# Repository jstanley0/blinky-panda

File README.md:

# blinky-panda
an electronic art project, basically

I made this for the design challenge, to learn KiCad better, to test out fabrication of a non-rectangular board, and for soldering practice.

There are 25 LEDs logically arranged in a 5x5 matrix, and a simple timer-driven program that drives them with independent 6-bit software PWM.

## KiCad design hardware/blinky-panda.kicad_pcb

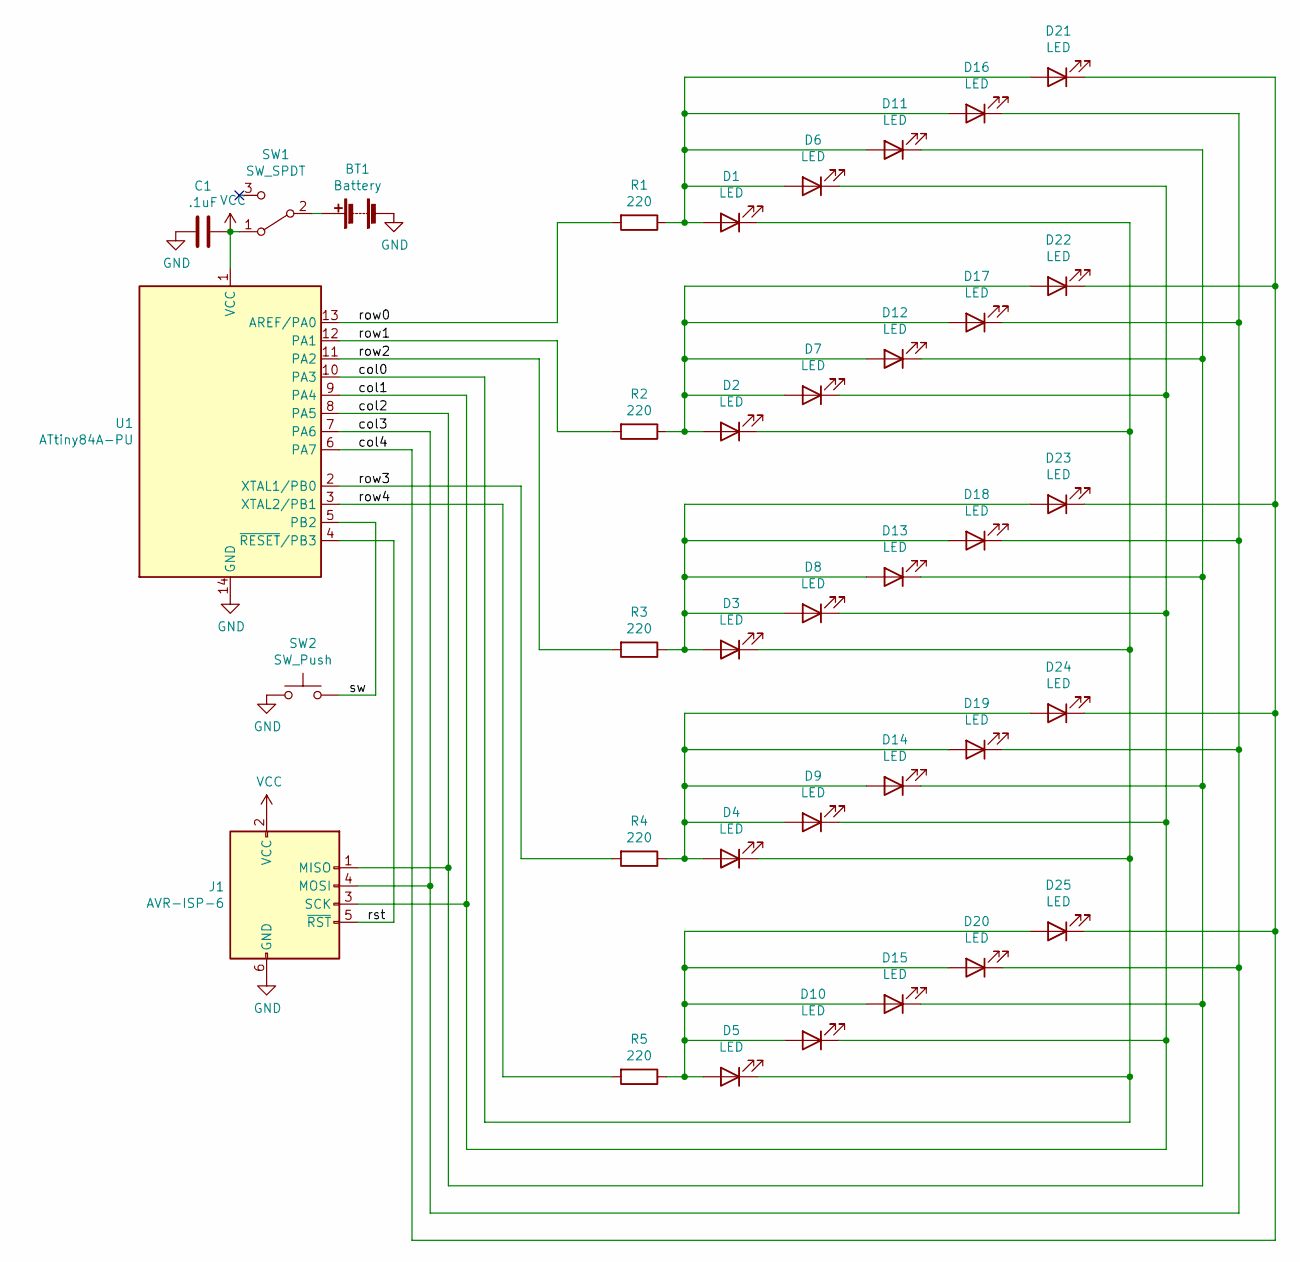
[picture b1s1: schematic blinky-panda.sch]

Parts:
BT1: Battery; PinHeader_1x02_P2.54mm_Vertical
C1: .1uF; C_Disc_D3.0mm_W1.6mm_P2.50mm
D1, D2, D3, D4, D5, D6, D7, D8, D9, D10, D11, D12, D13, D14, D15, D16, D17, D18, D19, D20, D21, D22, D23, D24, D25: LED; LED_D5.0mm_Clear
J1: AVR-ISP-6; PinHeader_2x03_P2.54mm_Vertical
R1, R2, R3, R4, R5: 220; R_Axial_DIN0204_L3.6mm_D1.6mm_P7.62mm_Horizontal
SW1: SW_SPDT; Switch_Slide_11.6x4mm_EG1218
SW2: SW_Push; SW_Tactile_Straight_KSL0Axx1LFTR
U1: ATtiny84A-PU; DIP-14_W7.62mm

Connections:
/col0: D1.1 (K), D2.1 (K), D3.1 (K), D4.1 (K), D5.1 (K), U1.10 (PA3)
/col1: D6.1 (K), D7.1 (K), D8.1 (K), D9.1 (K), D10.1 (K), J1.3 (SCK), U1.9 (PA4)
/col2: D11.1 (K), D12.1 (K), D13.1 (K), D14.1 (K), D15.1 (K), J1.1 (MISO), U1.8 (PA5)
/col3: D16.1 (K), D17.1 (K), D18.1 (K), D19.1 (K), D20.1 (K), J1.4 (MOSI), U1.7 (PA6)
/col4: D21.1 (K), D22.1 (K), D23.1 (K), D24.1 (K), D25.1 (K), U1.6 (PA7)
/row0: R1.2, U1.13 (AREF/PA0)
/row1: R2.2, U1.12 (PA1)
/row2: R3.2, U1.11 (PA2)
/row3: R4.2, U1.2 (XTAL1/PB0)
/row4: R5.2, U1.3 (XTAL2/PB1)
/rst: J1.5 (~RST), U1.4 (~RESET~/PB3)
/sw: SW2.2, U1.5 (PB2)
GND: BT1.2 (-), C1.2, J1.6 (GND), SW2.1, U1.14 (GND)
unnamed: BT1.1 (+), SW1.2 (B)
unnamed: D1.2 (A), D6.2 (A), D11.2 (A), D16.2 (A), D21.2 (A), R1.1
unnamed: D5.2 (A), D10.2 (A), D15.2 (A), D20.2 (A), D25.2 (A), R5.1
unnamed: D2.2 (A), D7.2 (A), D12.2 (A), D17.2 (A), D22.2 (A), R2.1
unnamed: D3.2 (A), D8.2 (A), D13.2 (A), D18.2 (A), D23.2 (A), R3.1
unnamed: D4.2 (A), D9.2 (A), D14.2 (A), D19.2 (A), D24.2 (A), R4.1
VCC: C1.1, J1.2 (VCC), SW1.1 (A), U1.1 (VCC)

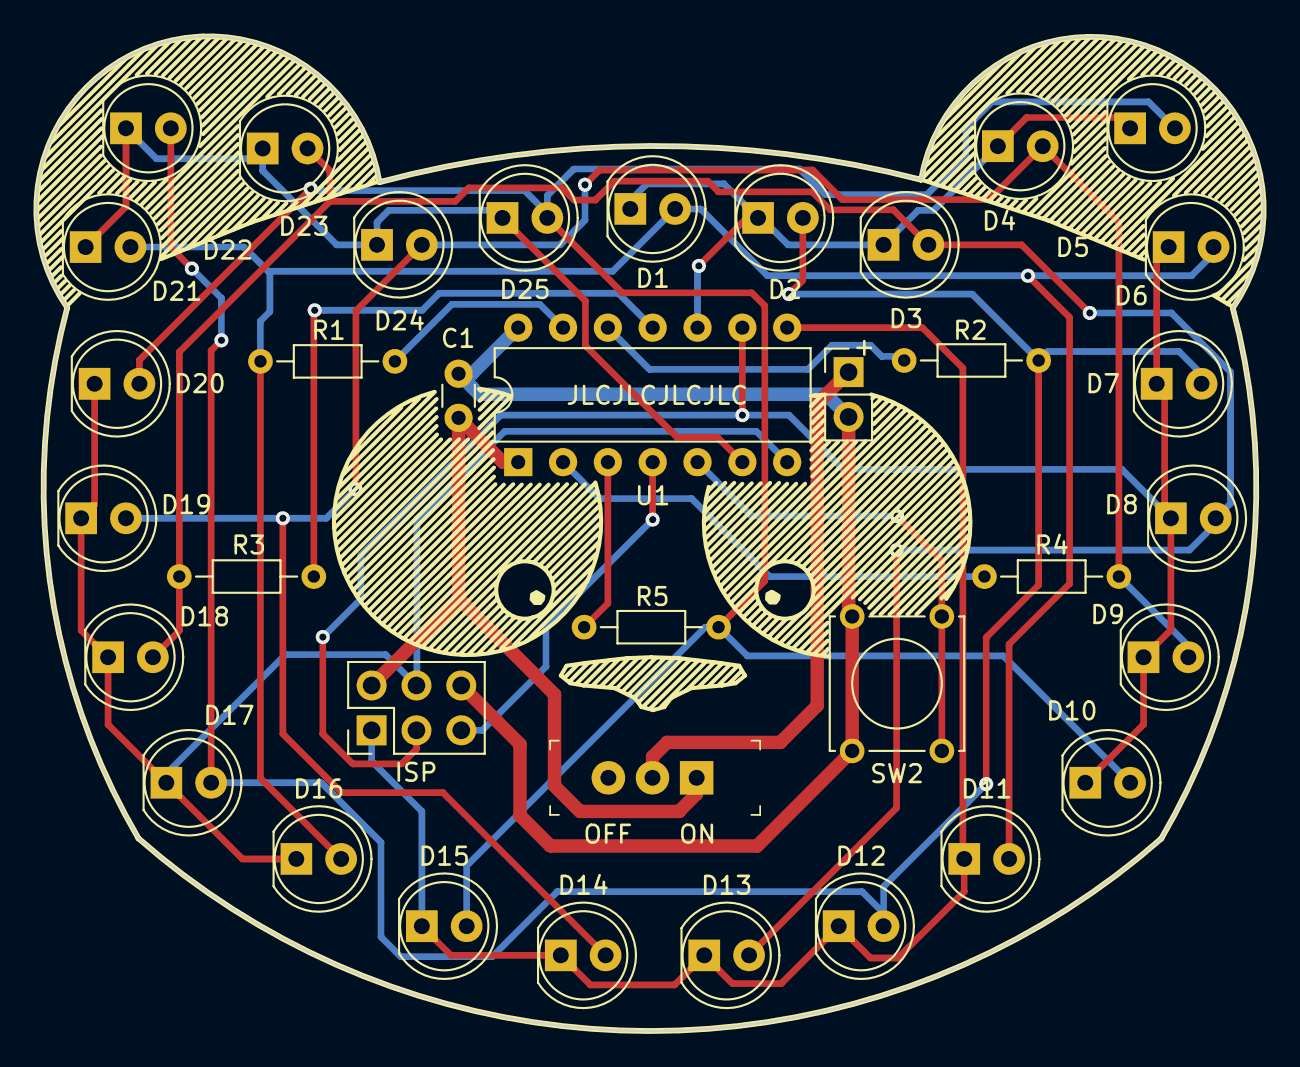
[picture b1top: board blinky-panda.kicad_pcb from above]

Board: 2 copper layers, 69.5 x 56.4 mm, 36 parts (0 on the bottom side), 20 nets.

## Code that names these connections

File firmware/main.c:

// blinky-panda
// (c) 2021 by Jeremy Stanley

// port assignments:
// PA0..PA2 -> row0..row2 anodes
// PA3..PA7 -> col0..col4 cathodes
// PB0..PB1 -> row3..row4 anodes
// PB2      -> tactile switch

// amount of time to spend on a single pattern, in milliseconds
// (note this is an unsigned 16-bit value)
#define PATTERN_MS 10000

#include <avr/io.h>
#include <avr/pgmspace.h>
#include <avr/sleep.h>
#include <avr/interrupt.h>
#include <util/delay.h>
#include <stdlib.h>

#define COL_ON(col) PORTA = 0b11111000 ^ (0b1000 << col); PORTB &= 0b11111100

// for software-PWM performance reasons this is all unrolled
// also this avoids conditionals over which port to address
#define ROW_0_ON() PORTA |= 1
#define ROW_0_OFF() PORTA &= ~1
#define ROW_1_ON() PORTA |= 0b10
#define ROW_1_OFF() PORTA &= ~0b10
#define ROW_2_ON() PORTA |= 0b100
#define ROW_2_OFF() PORTA &= ~0b100
#define ROW_3_ON() PORTB |= 1
#define ROW_3_OFF() PORTB &= ~1
#define ROW_4_ON() PORTB |= 0b10
#define ROW_4_OFF() PORTB &= ~0b10

#define BUTTON_STATE() (PINB & (1 << PB2))

void init_io()
{
  DDRA  = 0b11111111;
  PORTA = 0b11111000;
  DDRB  = 0b00000011;
  PORTB = 0b00000100;
}

void init_timer()
{
    TCCR0B = (1 << CS00);
    TIMSK0 = (1 << TOIE0);
}

volatile uint8_t framebuf[25] = {0};

ISR(TIM0_OVF_vect)
{
    static uint8_t count = 0;
    static uint8_t col = 0, base = 0;

    if (count == 0) {
        // switch column and clear rows
        if (++col == 5) {
            col = 0;
            base = 0;
        } else {
            base += 5;
        }
        COL_ON(col);

        // enable rows that are on
        if (framebuf[base]) ROW_0_ON();
        if (framebuf[base+1]) ROW_1_ON();
        if (framebuf[base+2]) ROW_2_ON();
        if (framebuf[base+3]) ROW_3_ON();
        if (framebuf[base+4]) ROW_4_ON();

    } else {
        // turn off rows
        if (count >= framebuf[base]) ROW_0_OFF();
        if (count >= framebuf[base+1]) ROW_1_OFF();
        if (count >= framebuf[base+2]) ROW_2_OFF();
        if (count >= framebuf[base+3]) ROW_3_OFF();
        if (count >= framebuf[base+4]) ROW_4_OFF();
    }

    count = (count + 1) & 0x3F;
}

void fade_out()
{
    for(uint8_t i = 0; i < 6; ++i) {
        for(uint8_t j = 0; j < 25; ++j) {
            framebuf[j] >>= 1;
        }
        _delay_ms(10);
    }
}

int update()
{
    static uint16_t pattern_ms = 0;

    uint8_t pre = BUTTON_STATE();
    _delay_ms(25);  // <- must be a compile-time constant
    pattern_ms += 25;

    // switch to the next pattern if the time limit on this one has been exceeded or the button has been pressed
    if ((pattern_ms >= PATTERN_MS) || (BUTTON_STATE() && !pre)) {
        pattern_ms = 0;
        fade_out();
        return 1;
    }

    return 0;
}

int fade()
{
    if (update())
        return 1;

    for(uint8_t z = 0; z < 25; ++z) {
        framebuf[z] >>= 1;
    }
    return 0;
}

void chase3()
{
  int8_t i = 0, j = rand() % 25, k = 13;
  for(;;) {
    framebuf[i] = 63;
    framebuf[j] = 127;
    framebuf[k] = 63;
    if (fade())
        break;
    if (++i >= 25)
      i = 0;
    if (i & 1) {
      if (--j < 0)
        j = 24;
    }
    if (++k >= 25)
      k = 0;
  }
}

void raindrops()
{
  for(;;) {
    for(int8_t i = 0; i < 3; ++i) {
        framebuf[rand() % 25] = 255;
    }
    if (fade())
        break;
  }
}

void shimmer()
{
    uint8_t i = 0;
    for(;;) {
        for(int8_t j = i; j < 25; j += 5) {
            framebuf[j] = 255;
        }
        if (fade())
            return;
        if (++i == 5)
            i = 0;
    }
}

void cycle()
{
    uint8_t i = 0, j = 0;
    for(;;) {
        for(int8_t j = i; j < 25; j += 5) {
            framebuf[j] = 63;
        }
        if (fade())
            return;
        if (++j == 2) {
            j = 0;
            if (++i == 5)
                i = 0;
        }
    }
}

void sparkle()
{
    for(;;)
    {
        for(int8_t i = 1; i < 64; i <<= 1) {
            for(int8_t j = 0; j < 25; ++j) {
                framebuf[j] = i;
            }
            if (update())
                return;
        }

        for(int8_t i = 63; i >= 0; --i) {
            for(int8_t j = 0; j < 25; ++j) {
                framebuf[j] = i;
            }
            framebuf[rand() % 25] = 63;
            if (fade())
                return;
        }

        for(int8_t i = 0; i < 10; ++i) {
            framebuf[rand() % 25] = 63;
                if (fade())
                    return;
        }
    }
}

int main(void)
{
  init_io();
  init_timer();

  sei();

  for(;;) {
    chase3();
    shimmer();
    raindrops();
    cycle();
    sparkle();
  }

}

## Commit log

2021-02-26 kind of a mess
2021-02-26 complete circuit
2021-02-28 darker shading
2021-02-28 rework pin assignments to fix isp
    I thought maybe it'd be a bad idea to have SCK connected to MOSI
    through a 220 ohm resistor.
    in this arrangement, power won't flow from one programming pin
    to another (they'll all hit reverse diodes)
2021-03-03 tagline
2021-03-26 test
2021-03-26 8MHz
2021-03-27 four-and-a-half-bit glitchy PWM
2021-03-27 a different approach
2021-03-27 Revert "a different approach"
    that was supposed to go in a branch but I fail at git
    This reverts commit 89ce5d6298b26ac84308afc0da870f66a3a9225a.
2021-03-27 six-bit not-obviously-glitchy PWM
    with 97Hz effective refresh rate!
2021-03-28 add animated gif demo
2021-03-28 slightly more elaborate demo
2021-04-03 some patterns
